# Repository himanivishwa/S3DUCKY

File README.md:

# S3 Ducky

A pocket-sized USB HID injection tool built on the ESP32-S3's native USB peripheral — no separate USB-serial or "Digispark"-style bootloader chip needed. Plug it in, and it enumerates as a keyboard.

> **NOTE: Firmware is not tested.**

*(Add renders or photos of the front/back PCB here — e.g. exported from KiCad's 3D viewer or your fab's preview.)*

## Why I built this

I had no experience in making devboards from esp32 dev modules so this is the best practical project i could think of aside from making a simple devboard

## Features

- **Native USB HID keyboard** — the ESP32-S3's built-in USB-OTG peripheral emulates a keyboard directly; no USB-to-serial bridge or second MCU in the path.
- **ESP32-S3-WROOM-1 module** — also brings Wi-Fi and BLE on board for future expansion (e.g. wireless trigger, exfil, or OTA payload updates).
- **Single-button payload trigger** — a press on the BOOT button (GPIO0) fires the macro in `triggerMacro()`.
- **Two onboard push buttons (SW1, SW2)** — serve as the BOOT (GPIO0) and EN/RESET buttons needed to manually enter flashing mode
- **Status LEDs** — onboard red, green and blue 0805 LEDs (D1–D3) for state/feedback.
- **Two 11-pin headers (J1, J3)** — breakout for spare GPIO.
- **Compact 2-layer PCB** — roughly 33 × 37 mm, SMD passives throughout.
- **USB-A male, through-hole** — plugs straight into a host port like a standard USB drive/dongle; no cable needed.

## How it works

The ESP32-S3 has a native USB-OTG peripheral, so it can act as a USB HID device entirely in firmware (via the Arduino `USBHIDKeyboard` library) — the chip itself is the keyboard, nothing is emulated over serial.

On boot, the firmware initializes the keyboard HID driver and the USB peripheral. The main loop watches the BOOT button (GPIO0, debounced) for a press. On a press, `triggerMacro()` sends a scripted sequence of keystrokes to whatever host the board is plugged into — the included example opens the Windows Run dialog (`GUI + R`), launches Notepad, and types a short message, release-all-keys between each step to avoid stuck inputs.

## Flashing

1. Install the ESP32 board package in Arduino IDE (or PlatformIO) and select **ESP32S3 Dev Module**.
2. Under **Tools**, set:
   - **USB Mode:** `USB-OTG (TinyUSB)` — required for native HID.
   - **USB CDC On Boot:** as needed for your debug setup.
3. If the board doesn't auto-enter the bootloader (no auto-reset circuit on this design), hold **SW1 (BOOT)**, tap **SW2 (RESET)**, then release SW1 to enter download mode.
4. Select the correct COM/serial port and upload `HID_firmware.ino`.
5. Reset the board and confirm it enumerates on the host as a USB keyboard before relying on it.

## Repo contents

| File | Description |
|---|---|
| `s3-ducky.kicad_pro` / `.kicad_sch` / `.kicad_pcb` | KiCad 9 project, schematic and PCB layout |
| `s3-ducky-*.gbr`, `*.drl`, `*.gbrjob` | Fabrication Gerbers / drill files / job file |
| `s3duckygerber.zip` | Zipped Gerber set, ready to send to a fab |
| `HID_firmware.ino` | Arduino sketch — native USB HID keyboard + button-triggered macro |
| `BOMS3DUCKY.csv` | Sourced bill of materials (see below) |

## Bill of Materials

Prices below are what I found while sourcing parts for a single board, mostly from Indian component shops (Robu, Quartz Components, Sharvi Electronics). `Unsourced` rows weren't matched to a confirmed listing — check stock/pricing yourself before ordering.

| # | Reference | Part | Footprint | Qty | Vendor | Product | Price (₹) | Price ($) |
|---|---|---|---|---|---|---|---|---|
| 1 | C1, C7 | 100nF | `Capacitor_SMD:C_0805_2012Metric` | 2 | Sharvi | [0.1uF/100nF 10V Capacitor – 0805 Package](https://sharvielectronics.com/product/0-1uf-100nf-10v-capacitor-0805-pack-of-10/) | 25 | 0.26 |
| 2 | C2, C5 | 10uF | `Capacitor_SMD:C_0805_2012Metric` | 2 | Sharvi | [10uF/10000nF 16V Capacitor – 0805 SMD Package](https://sharvielectronics.com/product/10uf-10000nf-16v-capacitor-%c2%b110-tolerance-0805x106k160ct-0805-package/) | 29.50 | 0.31 |
| 3 | C6 | 22uF | `Capacitor_SMD:C_0805_2012Metric` | 1 | Unsourced | [22uF 0805 X5R 10V](https://sharvielectronics.com/product/22uf-22000nf-50v-capacitor-%c2%b110-tolerance-0805b226k500ct-0805-package/) | 4.56 | 0.048 |
| 4 | D1 | RED LED | `LED_SMD:LED_0805_2012Metric` | 1 | Quartz | [Red LED – SMD (0805), Pack of 50](https://quartzcomponents.com/products/red-led-smd-0805-package-pack-of-50) | 25 | 0.26 |
| 5 | D2 | GREEN LED | `LED_SMD:LED_0805_2012Metric` | 1 | Quartz | [Green LED – SMD (0805), Pack of 50](https://quartzcomponents.com/collections/smd-leds/products/green-led-smd-0805-package-pack-of-50) | 24 | 0.26 |
| 6 | D3 | BLUE LED | `LED_SMD:LED_0805_2012Metric` | 1 | Quartz | [Blue LED – SMD (0805), Pack of 50](https://quartzcomponents.com/products/blue-led-smd-0805-package-pack-of-50) | 24 | 0.26 |
| 7 | J1, J3 | 1x11 male header, 2.54 mm | `PinHeader_1x11_P2.54mm_Vertical` | 2 | Unsourced | 1x40 break-away male header strip | — | — |
| 8 | J2 | USB_A (male, through-hole) | `usb_afoot:USB-AM-TH_AM90` | 1 | Robu | [USB A-type Plug Male PCB R/A Connector (Pack of 5)](https://robu.in/product/usb-a-type-plug-male-pcb-r-a-connector-pack-of-5) | 5 | 0.053 |
| 9 | R3, R4, R5, R6 | 5.1k | `Resistor_SMD:R_0805_2012Metric` | 4 | Quartz | [5.1K ohm 5% SMD Resistor 0805 (Pack of 20)](https://quartzcomponents.com/collections/smd-resistors/products/5-1k-ohm-5k1-5-smd-resistor-0805-pack-of-20-pieces) | 8 | 0.084 |
| 10 | SW1, SW2 | SMD tact switch ~3.9 × 3.0 mm | `smd_sw:SW-SMD_L3.9-W3.0-P4.45` | 2 | Unsourced | [SMD tactile switch, 20 pcs](https://robu.in/product/362-5mm-tactile-push-button-switch-20pcs/) | 25 | 0.26 |
| 11 | U1 | ESP32-S3-WROOM-1 | `RF_Module:ESP32-S3-WROOM-1` | 1 | Robu | [Espressif ESP32-S3-WROOM-1-N16R8 Module](https://robu.in/product/espressif-esp32-s3-wroom-1-n16r8-module) | 449 | 4.73 |
| 12 | U2 | LD1117V (3.3V, SOT-223 footprint) | `SOT-223-3_TabPin2` | 1 | Robu | [LM1117GS-3.3 1A LDO, SOT-223 (pin-compatible sub)](https://robu.in/product/lm1117gs-3-3-3-3v-lm1117-1a-fixed-output-ldo-linear-voltage-regulator-4-pin-sot-223/) | 25 | 0.26 |

### Shipping, tax & fab

| Item | Price (₹) | Price ($) |
|---|---|---|
| Robu shipping | 49 | 0.52 |
| Quartz shipping + taxes | 74.58 | 0.79 |
| Sharvi Electronics shipping + taxes | 68.20 | 0.72 |
| JLCPCB (PCB fab) | 379.78 | 4.00 |
| PCB shipping | 626.64 | 6.60 |
| **Total** | **₹1,842.26** | **$19.40** |

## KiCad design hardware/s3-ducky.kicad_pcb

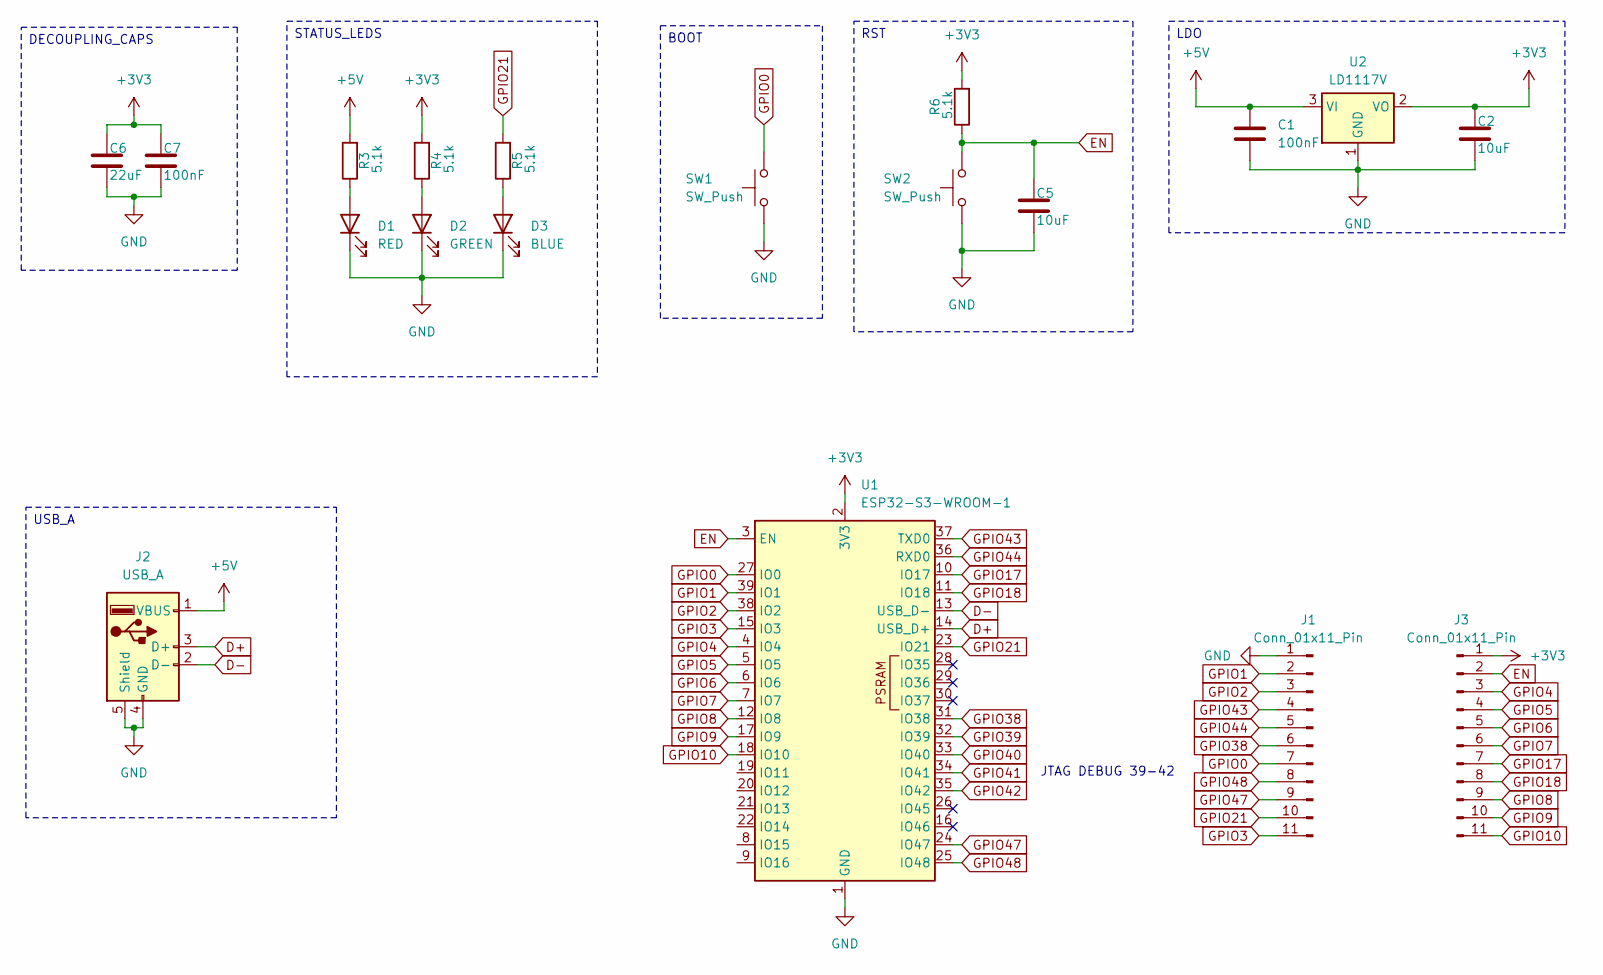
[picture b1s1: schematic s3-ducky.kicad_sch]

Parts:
C1, C7: 100nF; C_0805_2012Metric
C2, C5: 10uF; C_0805_2012Metric
C6: 22uF; C_0805_2012Metric
D1: RED; LED_0805_2012Metric
D2: GREEN; LED_0805_2012Metric
D3: BLUE; LED_0805_2012Metric
J1, J3: Conn_01x11_Pin; PinHeader_1x11_P2.54mm_Vertical
J2: USB_A; USB-AM-TH_AM90
R3, R4, R5, R6: 5.1k; R_0805_2012Metric
SW1, SW2: SW_Push; SW-SMD_L3.9-W3.0-P4.45
U1: ESP32-S3-WROOM-1
U2: LD1117V; SOT-223-3_TabPin2

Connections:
+3V3: C2.1, C6.1, C7.1, J3.1, R4.2, R6.2, U1.2 (3V3), U2.2 (VO)
+5V: C1.1, J2.1 (VBUS), R3.2, U2.3 (VI)
D+: J2.3 (D+), U1.14 (USB_D+)
D-: J2.2 (D-), U1.13 (USB_D-)
EN: C5.1, J3.2, R6.1, SW2.2, U1.3 (EN)
GND: C1.2, C2.2, C5.2, C6.2, C7.2, D1.1 (K), D2.1 (K), D3.1 (K), J1.1, J2.4 (GND), J2.5 (Shield), SW1.1, SW2.1, U1.1 (GND), U1.40 (GND), U1.41 (GND), U2.1 (GND)
GPIO0: J1.7, SW1.2, U1.27 (IO0)
GPIO1: J1.2, U1.39 (IO1)
GPIO2: J1.3, U1.38 (IO2)
GPIO3: J1.11, U1.15 (IO3)
GPIO4: J3.3, U1.4 (IO4)
GPIO5: J3.4, U1.5 (IO5)
GPIO6: J3.5, U1.6 (IO6)
GPIO7: J3.6, U1.7 (IO7)
GPIO8: J3.9, U1.12 (IO8)
GPIO9: J3.10, U1.17 (IO9)
GPIO10: J3.11, U1.18 (IO10)
GPIO17: J3.7, U1.10 (IO17)
GPIO18: J3.8, U1.11 (IO18)
GPIO21: J1.10, R5.2, U1.23 (IO21)
GPIO38: J1.6, U1.31 (IO38)
GPIO39: U1.32 (IO39)
GPIO40: U1.33 (IO40)
GPIO41: U1.34 (IO41)
GPIO42: U1.35 (IO42)
GPIO43: J1.4, U1.37 (TXD0)
GPIO44: J1.5, U1.36 (RXD0)
GPIO47: J1.9, U1.24 (IO47)
GPIO48: J1.8, U1.25 (IO48)
unnamed: D1.2 (A), R3.1
unnamed: D2.2 (A), R4.1
unnamed: D3.2 (A), R5.1

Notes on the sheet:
JTAG DEBUG 39-42
STATUS_LEDS
RST
USB_A
BOOT
LDO
DECOUPLING_CAPS

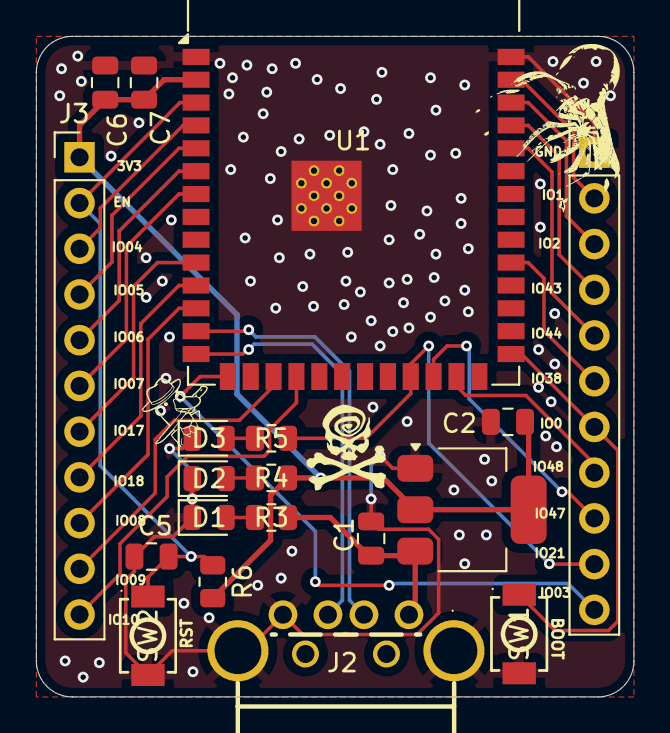
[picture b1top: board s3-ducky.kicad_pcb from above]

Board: 2 copper layers, 33.2 x 36.7 mm, 19 parts (0 on the bottom side), 28 nets.

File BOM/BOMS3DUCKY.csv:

#,Reference,Part (from your BOM),Footprint,Qty on board,Vendor,Product listed,Link,price,price in usd
1,"C1, C7",100nF,Capacitor_SMD:C_0805_2012Metric,2,Sharvi,0.1uF/100nF 10V Capacitor  0805 Package,https://sharvielectronics.com/product/0-1uf-100nf-10v-capaci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,25,0.26
2,"C2, C5",10uF,Capacitor_SMD:C_0805_2012Metric,2,Sharvi,10uF/10000nF 16V Capacitor  0805 SMD Package,https://sharvielectronics.com/product/10uf-10000nf-16v-capac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,29.5,0.31
3,C6,22uF,Capacitor_SMD:C_0805_2012Metric,1,Unsourced,22uF 0805 X5R 10V ,https://sharvielectronics.com/product/22uf-22000nf-50v-capac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,4.56,0.048
4,D1,RED LED,LED_SMD:LED_0805_2012Metric,1,Quartz,Red LED  SMD (0805 Package)  Pack of 50,https://quartzcomponents.com/products/red-led-smd-0805-packa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,25,0.26
5,D2,GREEN LED,LED_SMD:LED_0805_2012Metric,1,Quartz,Green LED  SMD (0805 Package)  Pack of 50,https://quartzcomponents.com/collections/smd-leds/products/g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,24,0.26
6,D3,BLUE LED,LED_SMD:LED_0805_2012Metric,1,Quartz,Blue LED  SMD (0805 Package)  Pack of 50,https://quartzcomponents.com/products/blue-led-smd-0805-pack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,24,0.26
7,"J1, J3","Conn_01x11_Pin (1x11 male header, 2.54 mm)",Connector_PinHeader_2.54mm:PinHeader_1x11_P2.54mm_Vertical,2,Unsourced,1x40 break-away male header strip ,n/a ,,
8,J2,"USB_A (male, through-hole)",usb_afoot:USB-AM-TH_AM90,1,Robu,USB A-type Plug Male PCB R/A Connector (Pack of 5),https://robu.in/product/usb-a-type-plug-male-pcb-r-a-connect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,5,0.053
9,"R3, R4, R5, R6",5.1k,Resistor_SMD:R_0805_2012Metric,4,Quartz,5.1K ohm / 5K1 5% SMD Resistor 0805 (Pack of 20 Pieces),https://quartzcomponents.com/collections/smd-resistors/produ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,8,0.084
10,"SW1, SW2",SW_Push (SMD tact switch ~3.9 × 3.0 mm),smd_sw:SW-SMD_L3.9-W3.0-P4.45,2,Unsourced,SMD tactile switch 3x4x2 mm (not found at the 4 shops),https://robu.in/product/362-5mm-tactile-push-button-switch-20pcs/,25,0.26
11,U1,ESP32-S3-WROOM-1,RF_Module:ESP32-S3-WROOM-1,1,Robu,Espressif ESP32-S3-WROOM-1-N16R8 Module,https://robu.in/product/espressif-esp32-s3-wroom-1-n16r8-module,449,4.73
12,U2,"LD1117V (3.3 V, SOT-223 footprint)",Package_TO_SOT_SMD:SOT-223-3_TabPin2,1,Robu,"LM1117GS-3.3  3.3V 1A LDO regulator, SOT-223 (pin-compatible substitute)",https://robu.in/product/lm1117gs-3-3-3-3v-lm1117-1a-fixed-ou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,25,0.26
,,,,,,,,,
,,,,,,robu shipping,,49,0.52
,,,,,,quartz shipping + taxes,,74.58,0.79
,,,,,,sharvielectronics shipping + taxes,,68.2,0.72
,,,,,,,,,
,,,,,,jlc pcb,,379.78,4
,,,,,,pcb shipping,,626.64,6.6
,,,,,,,,,
,,,,,,,Total,1842.26,19.4
